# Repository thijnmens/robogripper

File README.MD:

# 🤖 RoboGripper

RoboGripper is a robotic gripper system designed and built using **SolidWorks** for CAD design, **Arduino** for control, and integrated with a **URE robotic arm** platform. The project's purpose is to solve the Robot Gripper challenge of the Fontys AR course.

## Table of Contents
- [🤖 RoboGripper](#-robogripper)
  - [Table of Contents](#table-of-contents)
  - [🚀 Features](#-features)
  - [🛠️ Tech Stack](#️-tech-stack)
  - [⚙️ Setup \& Installation](#️-setup--installation)
    - [1. Hardware Assembly](#1-hardware-assembly)
    - [2. Software Setup](#2-software-setup)
  - [📸 Demo](#-demo)
  - [📜 License](#-license)

---

## 🚀 Features
- Custom-designed gripper modeled in **SolidWorks**
- Controlled via **Arduino microcontroller**, developed in C#
- The gripper is attached to a **URE robotic arm** programmed to pick up two (or more!) objects
- Design was born as a bottles gripper, but can be used to grab other types of  (small) objects.

---

## 🛠️ Tech Stack
- **Hardware**: URE robotic arm, Arduino servo motors
- **Software**: 
  - [SolidWorks](https://www.solidworks.com/) (CAD modeling)
  - [Arduino IDE](https://www.arduino.cc/en/software) (firmware programming)
  - [URScript] (https://s3-eu-west-1.amazonaws.com/ur-support-site/115824/scriptManual_SW5.11.pdf) (Universal Robots scripting language)

---

## ⚙️ Setup & Installation

### 1. Hardware Assembly
1. 3D print the gripper parts from the **SolidWorks CAD models**.  
2. Attach the gripper to the **URE robotic arm** end effector mount.  
3. Wire the servo motors and **Ardiuno** to the given PCB base, which is already connected to the UR robot.
4. Load the program on arm's software through USB or other methods.

### 2. Software Setup
1. Install whatever flashing tool you prefer.
2. Clone this repository:  
   ```bash
   git clone https://github.com/thijnmens/robogripper.git
   cd robogripper
   cd firmware
3. Select your board and port, and flash onto the microcontroller using whatever tool at your disposal.

---

## 🎮 Usage

* The gripper cannot be called externally, the process is entirely automated.
* The URE robot has a few preset position for pickup and drop, as shown in image.
* As per request, the RED tape is to be considering a no-go zone, which limits the possible pick up and especially drop points. 
  The order of said pickup points matters due to physical restrictions of the UR arm.

---

## 📂 Repository Structure

```
robogripper/
│── cad/            # SolidWorks models & assemblies
│── firmware/       # Arduino code & sketches
  |── README.md     # Firmware overview
|── conf            # UR configuration
  |── README.md     # Conf overview
│── docs/           # Documentation & schematics
│── README.md       # Project overview
     
```

---

## 📸 Demo

---

## 📜 License

This project is licensed under the **MIT License** – see the [LICENSE](LICENSE) file for details.

---

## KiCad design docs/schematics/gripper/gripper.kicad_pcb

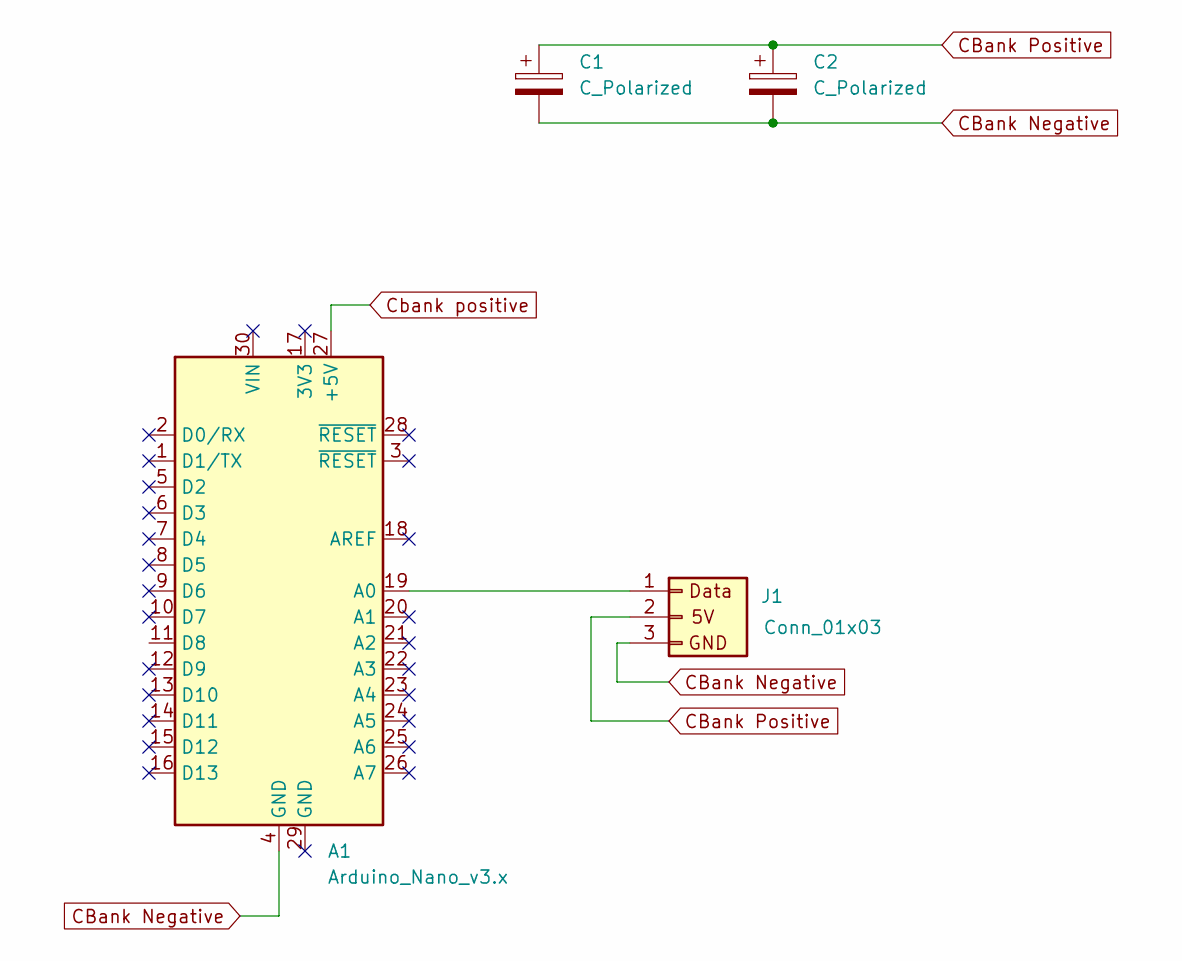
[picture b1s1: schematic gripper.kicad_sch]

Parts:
A1: Arduino_Nano_v3.x; Arduino_Nano
C1, C2: C_Polarized; CP_Radial_D10.0mm_P5.00mm
J1: Conn_01x03; PhoenixContact_GMSTBA_2,5_3-G-7,62_1x03_P7.62mm_Horizontal

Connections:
CBank Negative: A1.4 (GND), C1.2, C2.2, J1.3
CBank Positive: C1.1, C2.1, J1.2
Cbank positive: A1.27 (+5V)
unnamed: A1.19 (A0), J1.1

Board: 2 copper layers, 4 parts (0 on the bottom side), 3 nets, no tracks yet.

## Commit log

2025-09-02 Basic servo + sensor example
2025-09-02 make Clang-tidy happy :)
2025-09-02 Create codeql.yml (#1)
    * Create codeql.yml
    * Create pio.yml
    * Delete .github/workflows/codeql.yml
2025-09-02 Add clang tidy github action
2025-09-02 Update versions to latest
2025-09-02 Add correct permission
2025-09-02 simulation init and first few scripts
2025-09-02 readme adj
2025-09-02 Move pressure sensor code to component
2025-09-02 Add clang tidy github action (#2)
    * Add clang tidy github action
    * Update versions to latest
    * Add correct permission
    * Update .gitignore to support .idea
2025-09-02 Initialize pin in default PressureSensorComponent constructor
2025-09-02 Base position final, More initialization
2025-09-02 Add clang tidy configuration file
2025-09-02 Update constructor param initializers
2025-09-02 Fix typo in .clang-tidy
2025-09-02 Remove unknown keys
2025-09-02 Make clang not fail the quality gate
2025-09-02 Code Cleanup before merge with main
2025-09-02 Add basic robot messaging
2025-09-03 Readme additions, progress on the arm movements.
2025-09-03 deleted extra folder, pickup_target_two impl
2025-09-04 More improvements, readme adjustments
2025-09-04 Modification to program tree and single scripts.
2025-09-04 Finalized v1
2025-09-05 small changes (deprecated functions) + general improvements
2025-09-05 adjusting height
2025-09-08 improvements scripts + README.md
2025-09-08 moved firmware into its own folder
2025-09-08 moved ur3 conf into its own folder
2025-09-09 docs and some improvements
2025-09-09 schematics init
2025-09-09 changes!
2025-09-10 adjustments for 3.12
2025-09-10 execute drop action to aciton list
2025-09-10 pptx
2025-09-10 it fricking works
2025-09-14 everything else
2025-09-14 3d models
